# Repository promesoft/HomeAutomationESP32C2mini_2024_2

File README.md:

# HomeAutomationESP32C2mini_2024_2

 Kicad 8

# Purpose
Use for build into berker euro dåser

Two PSU modules and two uP modules

Additional power supply for +-12v and 5v for euro rack synth

## PSU
### 1 - Relay and 230V to 5v
### 2 - LED and 230V to 5v
## uP
### 1 - AM2320 and DS18B20
| ESP Designation  | Pin | Use |
| ------------- | ------------- | ------------- |
| U202 ESP32 C3 | GPIO05 | One Wire 18B20 |
| U202 ESP32 C3 | GPIO06 | SDA AM2320 / HDR |
| U202 ESP32 C3 | GPIO07 | SCL AM2320 / HDR |
| U202 ESP32 C3 | GPIO09 | LED |
| U202 ESP32 C3 | GPIO10 | Relay |
| U202 ESP32 C3 | GPIO21 | Relay Alternative |

### 2 - SSD1306 and AHT10
| ESP Designation  | Pin | Use |
| ------------- | ------------- | ------------- |
| U402 ESP32 C3 | GPIO05 | One Wire 18B20 |
| U402 ESP32 C3 | GPIO06 | SDA SSD1306 / AHT10 |
| U402 ESP32 C3 | GPIO07 | SCL SSD1306 / AHT10 |
| U402 ESP32 C3 | GPIO09 | LED |
| U402 ESP32 C3 | GPIO10 | Relay |
| U402 ESP32 C3 | GPIO21 | Relay Alternative |

## PSU for Euro rack - !!!!! EURORACK HEADER FLIPPED !!!!!!
+/-14v and 7v input

2x 16pin Eurorack power connectors as well as a +/-12v,5v,GND connector

Linear regulators 7805,7812,7912

Fuse blown detection with LED indication

# Status - Preliminary mounted
## Initial 
| Stage  | Detail | Status |
| ------------- | ------------- | ------------- |
| create material  | sch/pcb | OK  |
| | gerber | OK |
| production  |   | OK |
|  | produced | OK |
|  | delivered | OK? |
## Preliminary validation
| Test  | Detail | Status |
| ------------- | ------------- | ------------- |
| Initial Inspection | PWR RLY | OK |
| Initial Inspection | PWR |  |
| Initial Inspection | ESP32C3 OLED| RELAY not working |
|  | | OLED 0,96" not pin-compatible |
| Initial Inspection | ESP32C3 |  |
| Initial Technical Test | PWR RLY+ESP32C3 OLED AHT10 | OK - Blue LED req 820R - 10K pullup removed as impl in ESP32 pullup |
| Initial Technical Test |  |  |
| Initial Technical Test |  |  |
| Initial Product Test | PWR RLY+ESP32C3 OLED AHT10 | OK |
| Initial Product Test |  |  |
| Initial Product Test |  |  |
| Power Draw |  |  |
| Power Draw |  |  |
| Power Draw |  |  |

## Secondary validation
| Test  | Detail | Status |
| ------------- | ------------- |------------- |
| Product Test |  | |
| Product Test |  |  |
| Quality | | |
| Quality | | |
| Long Term Product Test |  |  |
| Power Draw |  |  |
| Power Draw |  |  |
| Power Draw |  |  |

## Errata
### Errata - Sub 1
### Errata - Sub 2
### Errata - Eurorack PSU - !!!!! EURORACK HEADER FLIPPED !!!!!!
| ERROR  | Detail | Workaround |
| ------------- | ------------- |------------- |
| J601 and J602 flipped | -12v on PIN 15+16 - should have been PIN 1+2 | FLIP the header compared to the silkscreen |

## Issues and Notes
### Sub 1
### Sub 2

# Pictures

# Inspiration
https://github.com/pforrmi/KiCad-SSD1306-128x64/tree/master

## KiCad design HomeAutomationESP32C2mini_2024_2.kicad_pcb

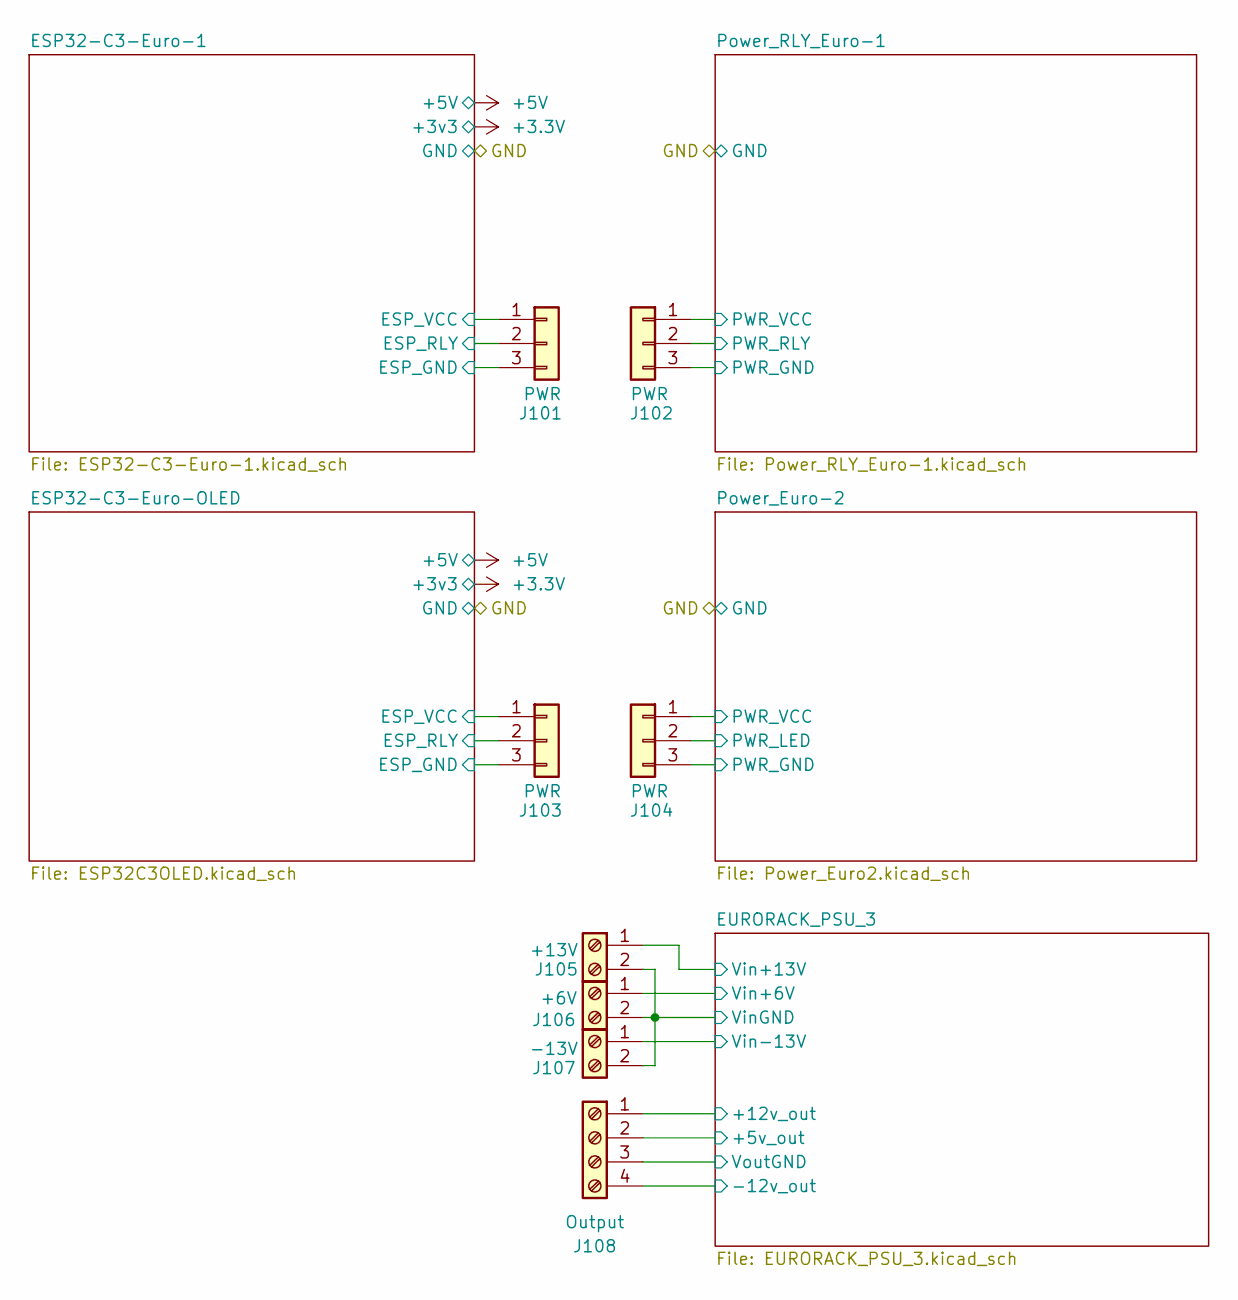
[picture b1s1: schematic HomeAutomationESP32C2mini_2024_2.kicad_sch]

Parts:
J101, J102, J103, J104: PWR; Pins_1x03_2.54mm_TH; Part Number 1-0301FBV0T
J105: +13V; JST_NV_B02P-NV_1x02_P5.00mm_Vertical
J106: +6V; JST_NV_B02P-NV_1x02_P5.00mm_Vertical
J107: -13V; JST_NV_B02P-NV_1x02_P5.00mm_Vertical
J108: Output; TerminalBlock_Phoenix_PT-1,5-4-5.0-H_1x04_P5.00mm_Horizontal

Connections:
/ESP32-C3-Euro-1/ESP_RLY: J101.2; also elsewhere on the board
/ESP32-C3-Euro-1/ESP_VCC: J101.1; also elsewhere on the board
/ESP32-C3-Euro-OLED/ESP_RLY: J103.2; also elsewhere on the board
/ESP32-C3-Euro-OLED/ESP_VCC: J103.1; also elsewhere on the board
/EURORACK_PSU_3/-12v_out: J108.4; also elsewhere on the board
/EURORACK_PSU_3/Vin+6V: J106.1; also elsewhere on the board
/EURORACK_PSU_3/Vin+13V: J105.1; also elsewhere on the board
/EURORACK_PSU_3/Vin-13V: J107.1; also elsewhere on the board
/GND: J101.3, J103.3, J104.3; also elsewhere on the board
/Power_Euro-2/PWR_LED: J104.2; also elsewhere on the board
/Power_Euro-2/PWR_VCC: J104.1; also elsewhere on the board
/Power_RLY_Euro-1/PWR_GND: J102.3; also elsewhere on the board
/Power_RLY_Euro-1/PWR_RLY: J102.2; also elsewhere on the board
/Power_RLY_Euro-1/PWR_VCC: J102.1; also elsewhere on the board

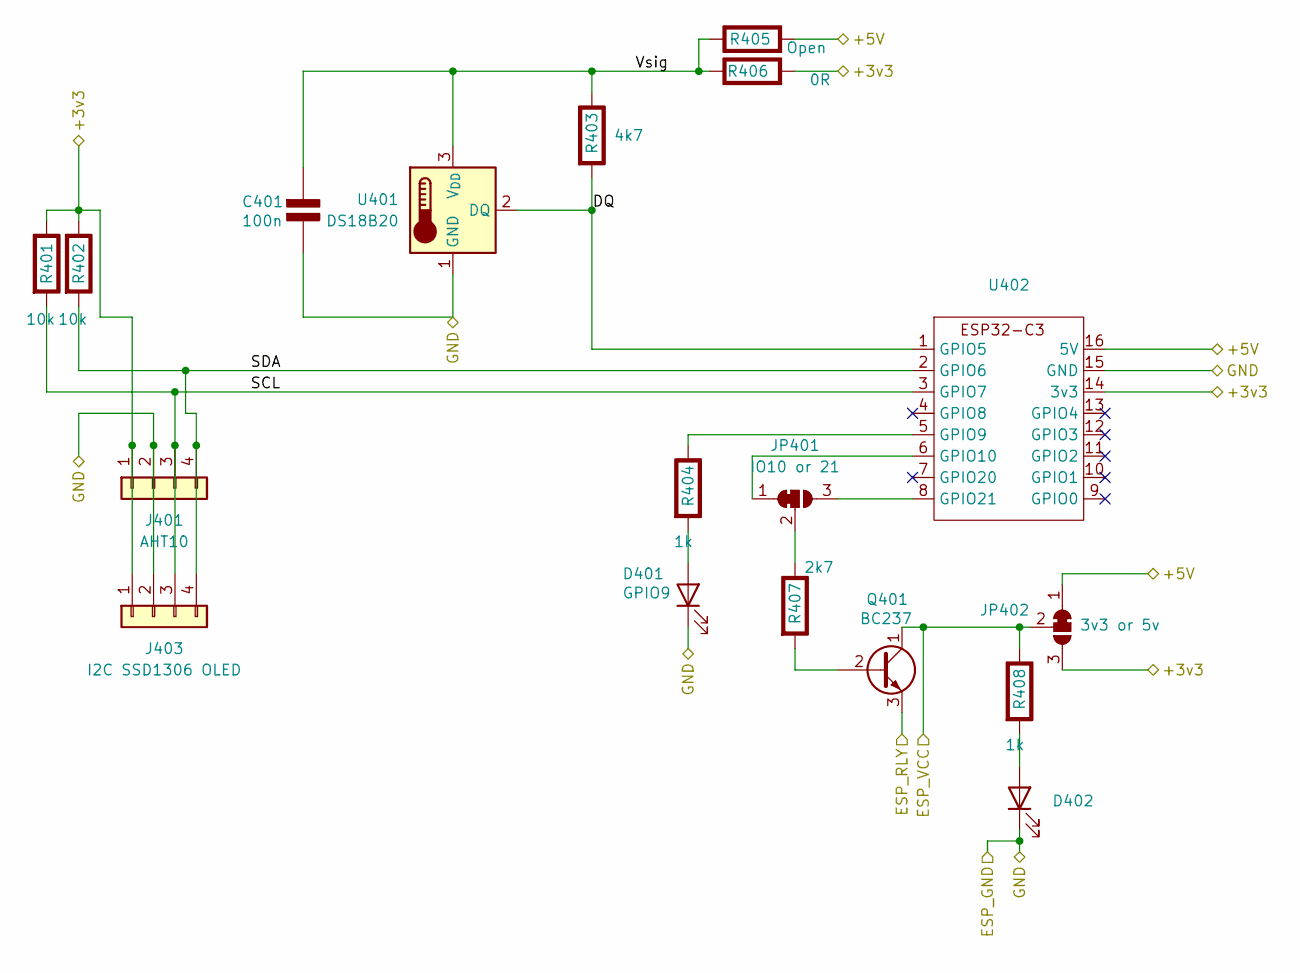
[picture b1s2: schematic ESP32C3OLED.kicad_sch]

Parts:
C401: 100n; C_0805_2012Metric; Rating V
D401: GPIO9; LED_D3.0mm
D402: PWR; LED_D3.0mm
J401: AHT10; Pins_1x04_2.54mm_TH
J403: I2C SSD1306 OLED; 128x64OLED
JP401: IO10 or 21; SolderJumper-3_P1.3mm_Bridged12_RoundedPad1.0x1.5mm_NumberL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
JP402: 3v3 or 5v; SolderJumper-3_P1.3mm_Bridged12_RoundedPad1.0x1.5mm_NumberL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
Q401: BC237; TO-92_Inline
R401, R402: 10k; R_0805_2012Metric; Rating W
R403: 4k7; R_0805_2012Metric; Rating W
R404, R408: 1k; R_0805_2012Metric; Rating W
R405: Open; R_0805_2012Metric; Rating W
R406: 0R; R_0805_2012Metric; Rating W
R407: 2k7; R_0805_2012Metric; Rating W
U401: DS18B20; TO-92_Inline
U402: ESP32-C3-Supermini

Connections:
+3.3V: J401.1, J403.1, JP402.3 (B), R401.1 (+), R402.1 (+), R406.2 (-), U402.14 (3v3); also elsewhere on the board
+5V: JP402.1 (A), R405.2 (-), U402.16 (5V); also elsewhere on the board
/ESP32-C3-Euro-OLED/DQ: R403.2 (-), U401.2 (DQ), U402.1 (GPIO5)
/ESP32-C3-Euro-OLED/ESP_RLY: Q401.3 (E); also elsewhere on the board
/ESP32-C3-Euro-OLED/ESP_VCC: JP402.2 (C), Q401.1 (C), R408.1 (+); also elsewhere on the board
/ESP32-C3-Euro-OLED/SCL: J401.3, J403.3, R401.2 (-), U402.3 (GPIO7)
/ESP32-C3-Euro-OLED/SDA: J401.4, J403.4, R402.2 (-), U402.2 (GPIO6)
/ESP32-C3-Euro-OLED/Vsig: C401.1 (+), R403.1 (+), R405.1 (+), R406.1 (+), U401.3 (V_{DD})
/GND: C401.2 (-), D401.1 (K), D402.1 (K), J401.2, J403.2, U401.1 (GND), U402.15 (GND); also elsewhere on the board
unnamed: D401.2 (A), R404.2 (-)
unnamed: D402.2 (A), R408.2 (-)
unnamed: JP401.1 (A), U402.6 (GPIO10)
unnamed: JP401.3 (B), U402.8 (GPIO21)
unnamed: JP401.2 (C), R407.1 (+)
unnamed: Q401.2 (B), R407.2 (-)
unnamed: R404.1 (+), U402.5 (GPIO9)

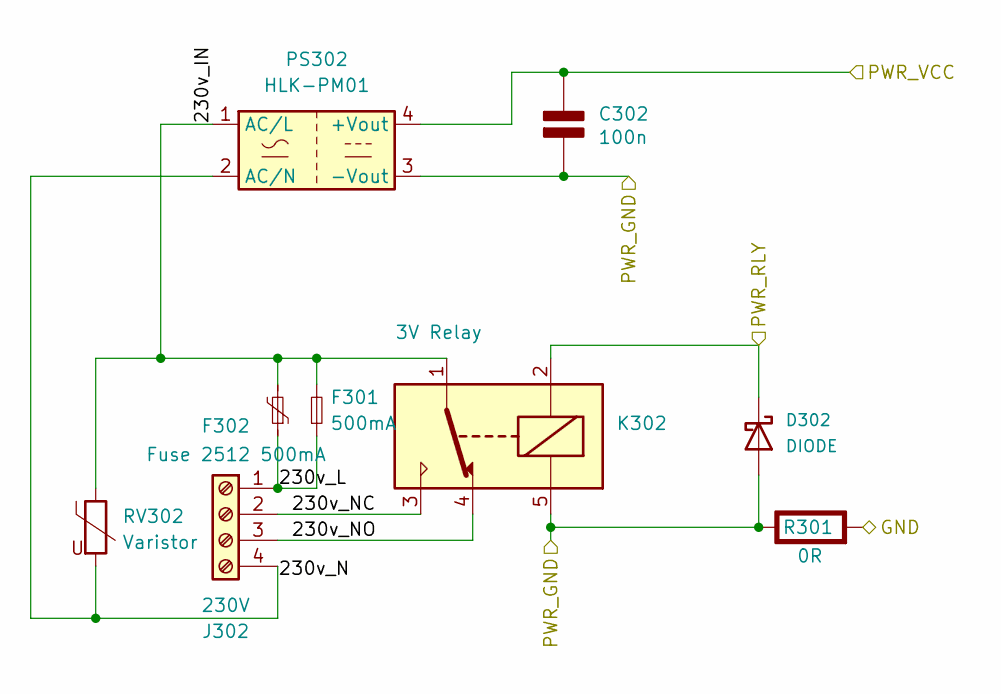
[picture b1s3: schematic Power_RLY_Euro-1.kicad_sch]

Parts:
C302: 100n; C_0805_2012Metric; Rating V
D302: DIODE; D_DO-41_SOD81_P10.16mm_Horizontal
F301: 500mA; Fuse_Littelfuse-NANO2-462
F302: Fuse 2512 500mA; Fuse_2512_6332Metric_Pad1.52x3.35mm_HandSolder
J302: 230V; TerminalBlock_Phoenix_PT-1,5-4-5.0-H_1x04_P5.00mm_Horizontal
K302: 3V Relay; Relay_SPDT_SANYOU_SRD_Series_Form_C
PS302: HLK-PM01; Converter_ACDC_Hi-Link_HLK-PMxx
R301: 0R; R_0805_2012Metric; Rating W
RV302: Varistor; RV_Disc_D9mm_W4.8mm_P5mm

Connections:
/GND: R301.2 (-); also elsewhere on the board
/Power_RLY_Euro-1/230v_IN: F301.2, F302.2, K302.1, PS302.1 (AC/L), RV302.1
/Power_RLY_Euro-1/230v_L: F301.1, F302.1, J302.1
/Power_RLY_Euro-1/230v_N: J302.4, PS302.2 (AC/N), RV302.2
/Power_RLY_Euro-1/230v_NC: J302.2, K302.3
/Power_RLY_Euro-1/230v_NO: J302.3, K302.4
/Power_RLY_Euro-1/PWR_GND: C302.2 (-), D302.2 (A), K302.5, PS302.3 (-Vout), R301.1 (+); also elsewhere on the board
/Power_RLY_Euro-1/PWR_RLY: D302.1 (K), K302.2; also elsewhere on the board
/Power_RLY_Euro-1/PWR_VCC: C302.1 (+), PS302.4 (+Vout); also elsewhere on the board

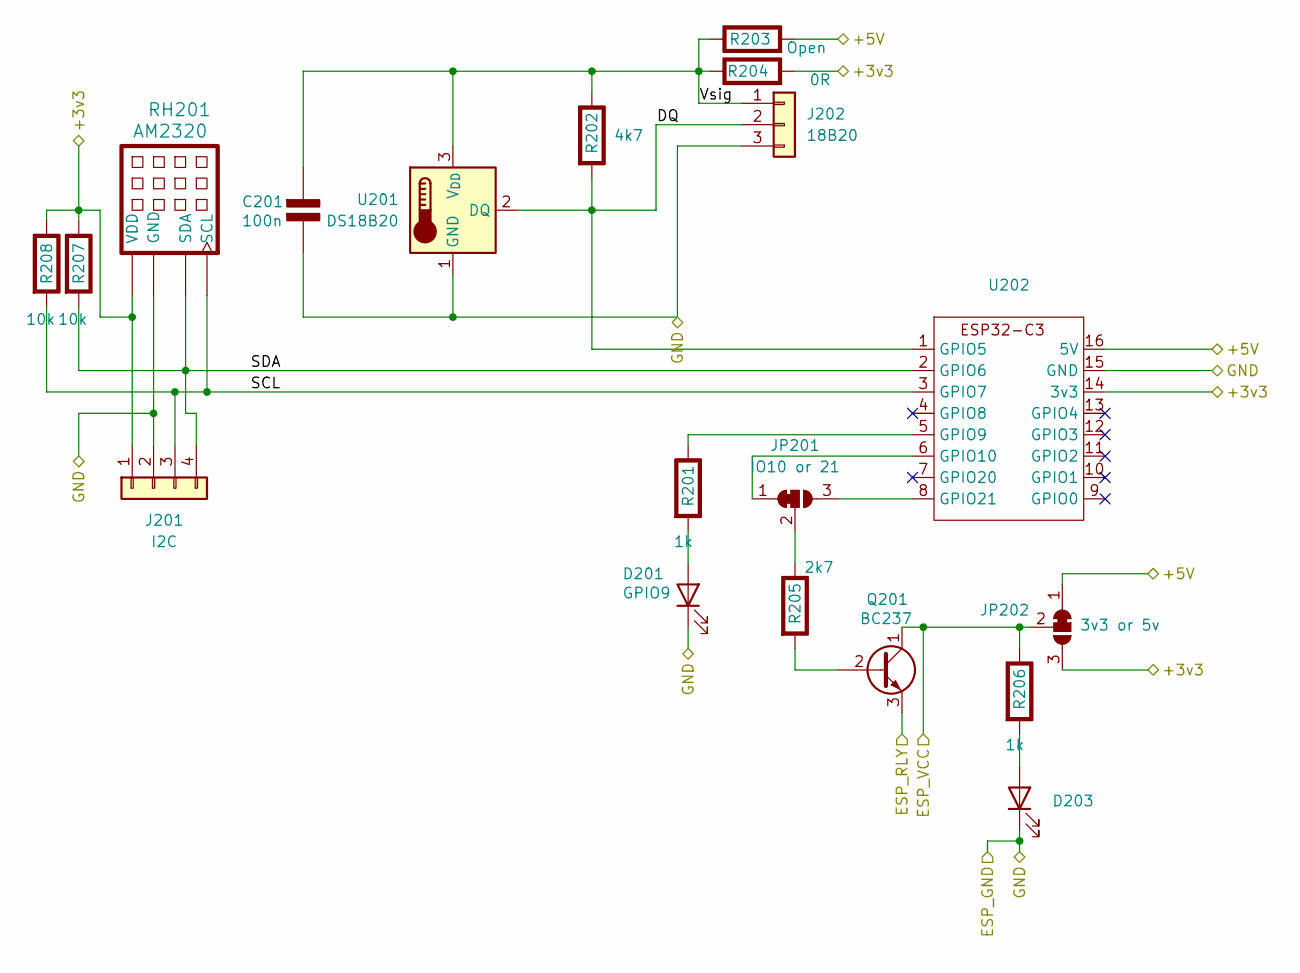
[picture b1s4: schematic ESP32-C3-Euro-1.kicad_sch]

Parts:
C201: 100n; C_0805_2012Metric; Rating V
D201: GPIO9; LED_D3.0mm
D203: PWR; LED_D3.0mm
J201: I2C; Pins_1x04_2.54mm_TH
J202: 18B20; Pins_1x03_2.54mm_TH; Part Number 1-0301FBV0T
JP201: IO10 or 21; SolderJumper-3_P1.3mm_Bridged12_RoundedPad1.0x1.5mm_NumberL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
JP202: 3v3 or 5v; SolderJumper-3_P1.3mm_Bridged12_RoundedPad1.0x1.5mm_NumberL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
Q201: BC237; TO-92_Inline
R201, R206: 1k; R_0805_2012Metric; Rating W
R202: 4k7; R_0805_2012Metric; Rating W
R203: Open; R_0805_2012Metric; Rating W
R204: 0R; R_0805_2012Metric; Rating W
R205: 2k7; R_0805_2012Metric; Rating W
R207, R208: 10k; R_0805_2012Metric; Rating W
RH201: AM2320; ASAIR_AM2302_P2.54mm_Vertical
U201: DS18B20; TO-92_Inline
U202: ESP32-C3-Supermini

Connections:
+3.3V: J201.1, JP202.3 (B), R204.2 (-), R207.1 (+), R208.1 (+), RH201.1 (VDD), U202.14 (3v3); also elsewhere on the board
+5V: JP202.1 (A), R203.2 (-), U202.16 (5V); also elsewhere on the board
/ESP32-C3-Euro-1/DQ: J202.2, R202.2 (-), U201.2 (DQ), U202.1 (GPIO5)
/ESP32-C3-Euro-1/ESP_RLY: Q201.3 (E); also elsewhere on the board
/ESP32-C3-Euro-1/ESP_VCC: JP202.2 (C), Q201.1 (C), R206.1 (+); also elsewhere on the board
/ESP32-C3-Euro-1/SCL: J201.3, R208.2 (-), RH201.4 (SCL), U202.3 (GPIO7)
/ESP32-C3-Euro-1/SDA: J201.4, R207.2 (-), RH201.2 (SDA), U202.2 (GPIO6)
/ESP32-C3-Euro-1/Vsig: C201.1 (+), J202.1, R202.1 (+), R203.1 (+), R204.1 (+), U201.3 (V_{DD})
/GND: C201.2 (-), D201.1 (K), D203.1 (K), J201.2, J202.3, RH201.3 (GND), U201.1 (GND), U202.15 (GND); also elsewhere on the board
unnamed: D201.2 (A), R201.2 (-)
unnamed: D203.2 (A), R206.2 (-)
unnamed: JP201.1 (A), U202.6 (GPIO10)
unnamed: JP201.3 (B), U202.8 (GPIO21)
unnamed: JP201.2 (C), R205.1 (+)
unnamed: Q201.2 (B), R205.2 (-)
unnamed: R201.1 (+), U202.5 (GPIO9)

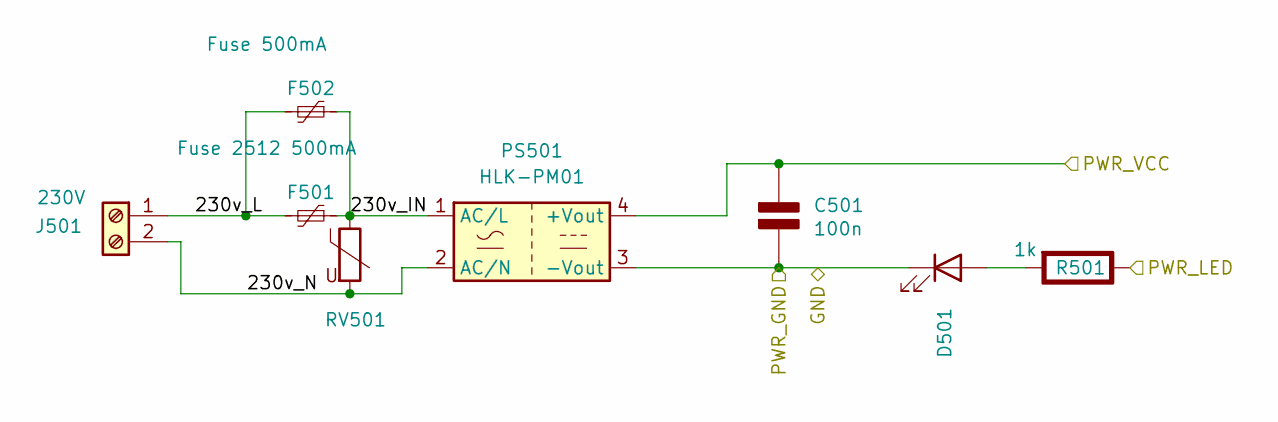
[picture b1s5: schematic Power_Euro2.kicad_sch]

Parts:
C501: 100n; C_0805_2012Metric; Rating V
D501: PWR; LED_0805_2012Metric_Pad1.15x1.40mm_HandSolder
F501: Fuse 2512 500mA; Fuse_2512_6332Metric_Pad1.52x3.35mm_HandSolder
F502: Fuse 500mA; L_Axial_L7.0mm_D3.3mm_P5.08mm_Vertical_Fastron_MICC
J501: 230V; JST_NV_B02P-NV_1x02_P5.00mm_Vertical
PS501: HLK-PM01; Converter_ACDC_Hi-Link_HLK-PMxx
R501: 1k; R_0805_2012Metric; Rating W
RV501: Varistor; RV_Disc_D9mm_W4.8mm_P5mm

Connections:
/GND: C501.2 (-), D501.1 (K), PS501.3 (-Vout); also elsewhere on the board
/Power_Euro-2/230v_IN: F501.1, F502.1, PS501.1 (AC/L), RV501.1
/Power_Euro-2/230v_L: F501.2, F502.2, J501.1
/Power_Euro-2/230v_N: J501.2, PS501.2 (AC/N), RV501.2
/Power_Euro-2/PWR_LED: R501.1 (+); also elsewhere on the board
/Power_Euro-2/PWR_VCC: C501.1 (+), PS501.4 (+Vout); also elsewhere on the board
unnamed: D501.2 (A), R501.2 (-)

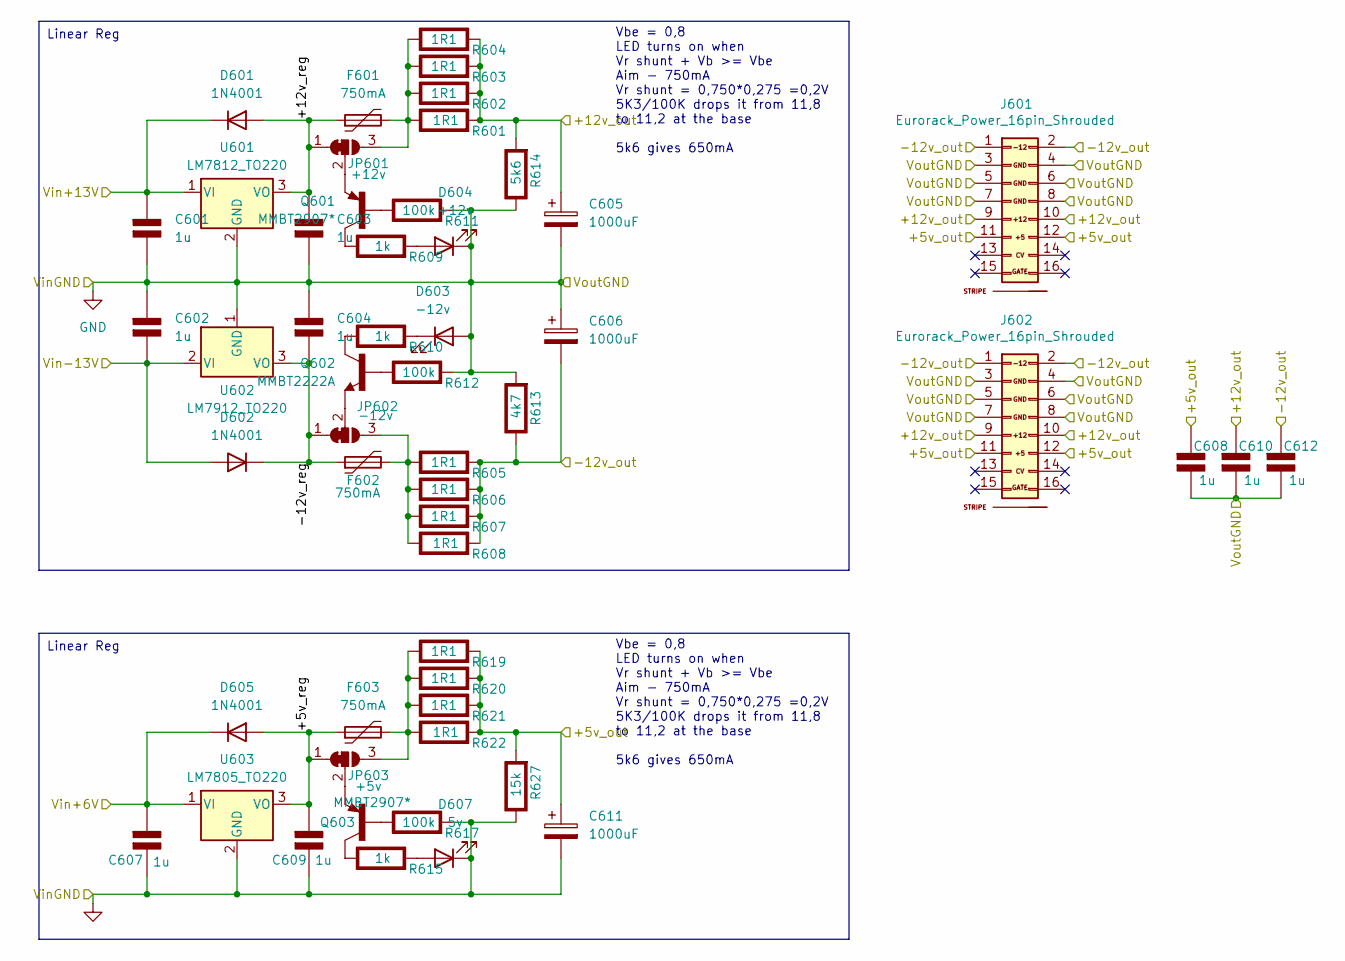
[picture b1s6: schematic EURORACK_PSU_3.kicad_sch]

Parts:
C601, C602, C603, C604, C607, C608, C609, C610, C612: 1u; C_0805_AJ; Rating V
C605, C606, C611: 1000uF; CP_Radial_D10.0mm_P5.00mm
D601, D602, D605: 1N4001; D_DO-41_SOD81_P10.16mm_Horizontal
D603: -12v; D_0805_AJ
D604: +12v; D_0805_AJ
D607: 5v; D_0805_AJ
F601, F602, F603: 750mA; Fuse_1812_4532Metric
J601, J602: Eurorack_Power_16pin_Shrouded; IDC-Header_2x08_P2.54mm_Vertical; Part Number LL1007-1 (2*8 HITEMP)
JP601: +12v; SolderJumper-3_P1.3mm_Bridged12_RoundedPad1.0x1.5mm_NumberL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
JP602: -12v; SolderJumper-3_P1.3mm_Bridged12_RoundedPad1.0x1.5mm_NumberL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
JP603: +5v; SolderJumper-3_P1.3mm_Bridged12_RoundedPad1.0x1.5mm_NumberL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
Q601, Q603: MMBT2907*; SOT-23
Q602: MMBT2222A; SOT-23
R601, R602, R603, R604, R605, R606, R607, R608, R619, R620, R621, R622: 1R1; R_0805_AJ; Rating W
R609, R610, R615: 1k; R_0805_AJ; Rating W
R611, R612, R617: 100k; R_0805_AJ; Rating W
R613: 4k7; R_0805_AJ; Rating W
R614: 5k6; R_0805_AJ; Rating W
R627: 15k; R_0805_AJ; Rating W
U601: LM7812_TO220; TO-220-3_Vertical
U602: LM7912_TO220; TO-220-3_Vertical
U603: LM7805_TO220; TO-220-3_Vertical

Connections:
/EURORACK_PSU_3/+5v_reg: C609.1 (+), D605.2 (A), F603.1, JP603.1 (A), U603.3 (VO)
/EURORACK_PSU_3/+12v_reg: C603.1 (+), D601.2 (A), F601.1, JP601.1 (A), U601.3 (VO)
/EURORACK_PSU_3/-12v_out: C606.2, C612.1 (+), J601.1, J601.2, J601.15 (-12V), J601.16, J602.1, J602.2, J602.15 (-12V), J602.16, R605.2 (-), R606.2 (-), R607.2 (-), R608.2 (-), R613.1 (+); also elsewhere on the board
/EURORACK_PSU_3/-12v_reg: C604.2 (-), D602.1 (K), F602.1, JP602.1 (A), U602.3 (VO)
/EURORACK_PSU_3/Vin+6V: C607.1 (+), D605.1 (K), U603.1 (VI); also elsewhere on the board
/EURORACK_PSU_3/Vin+13V: C601.1 (+), D601.1 (K), U601.1 (VI); also elsewhere on the board
/EURORACK_PSU_3/Vin-13V: C602.2 (-), D602.2 (A), U602.2 (VI); also elsewhere on the board
unnamed: D603.1 (K), R610.2 (-)
unnamed: D604.2 (A), R609.2 (-)
unnamed: D607.2 (A), R615.2 (-)
unnamed: F601.2, JP601.3 (B), R601.1 (+), R602.1 (+), R603.1 (+), R604.1 (+)
unnamed: JP601.2 (C), Q601.2 (E)
unnamed: F602.2, JP602.3 (B), R605.1 (+), R606.1 (+), R607.1 (+), R608.1 (+)
unnamed: JP602.2 (C), Q602.2 (E)
unnamed: F603.2, JP603.3 (B), R619.1 (+), R620.1 (+), R621.1 (+), R622.1 (+)
unnamed: JP603.2 (C), Q603.2 (E)
unnamed: Q601.1 (B), R611.1 (+)
unnamed: Q601.3 (C), R609.1 (+)
unnamed: Q602.1 (B), R612.1 (+)
unnamed: Q602.3 (C), R610.1 (+)
unnamed: Q603.1 (B), R617.1 (+)
unnamed: Q603.3 (C), R615.1 (+)

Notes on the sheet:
Linear Reg
Vbe = 0,8 LED turns on when Vr shunt + Vb >= Vbe Aim - 750mA Vr shunt = 0,750*0,275 =0,2V 5K3/100K drops it from 11,8 to 11,2 at the base 5k6 gives 650mA

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
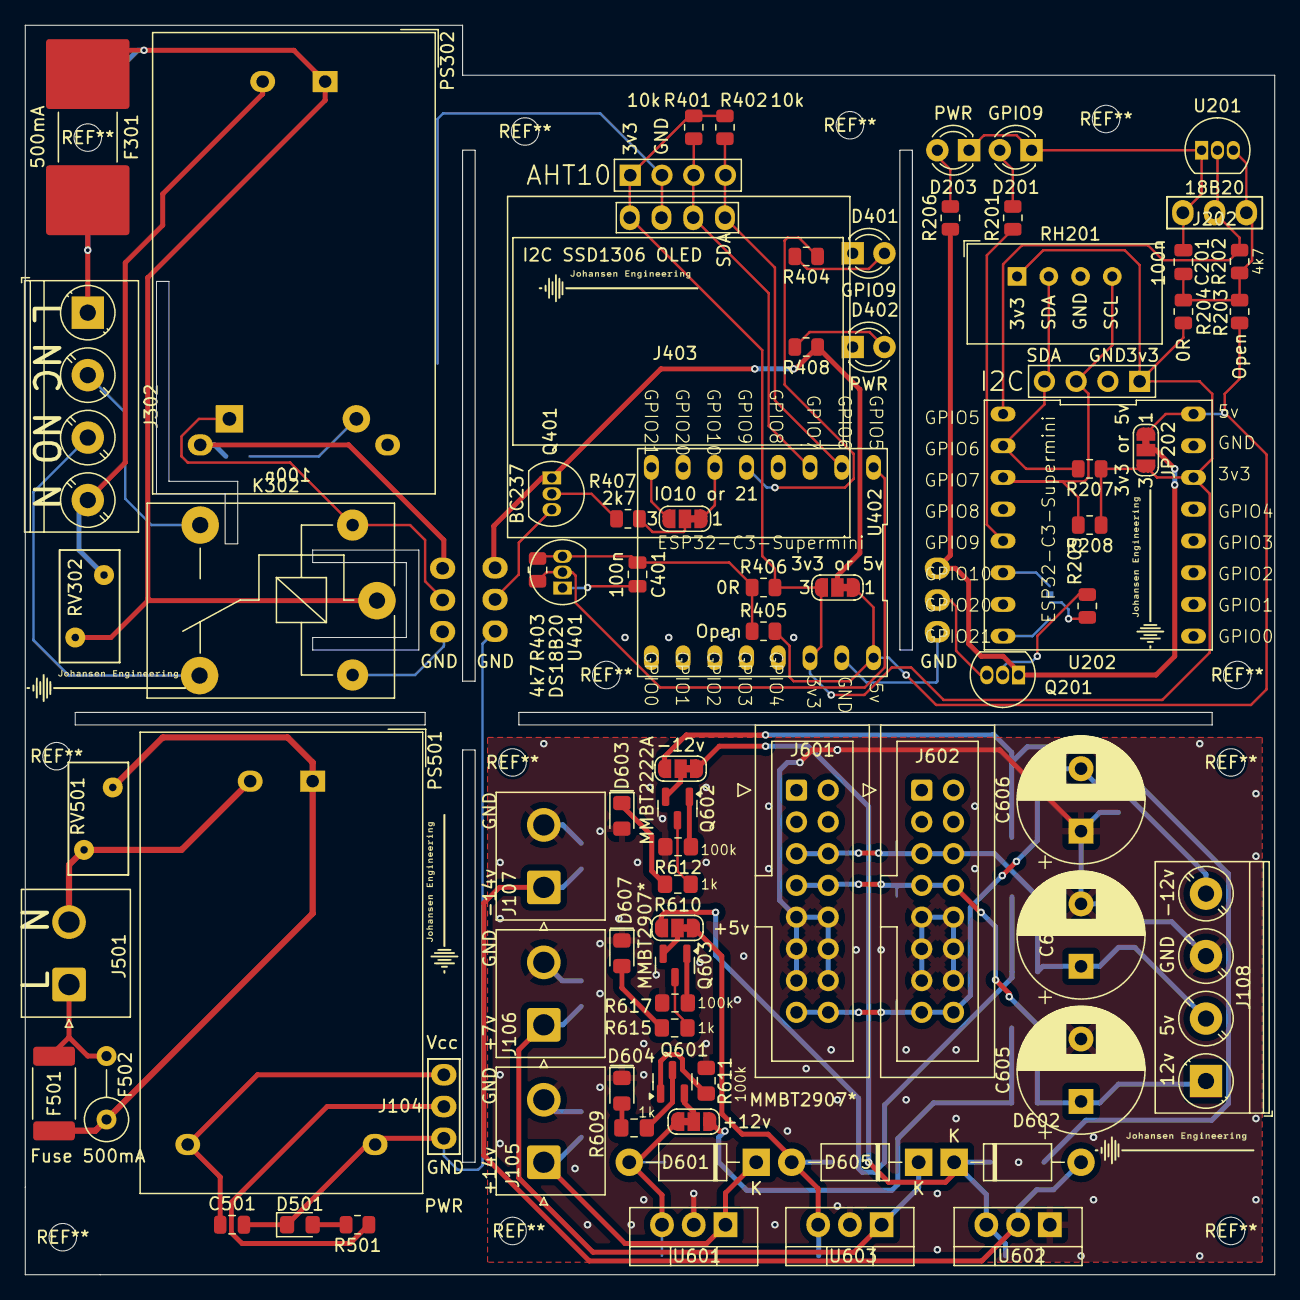
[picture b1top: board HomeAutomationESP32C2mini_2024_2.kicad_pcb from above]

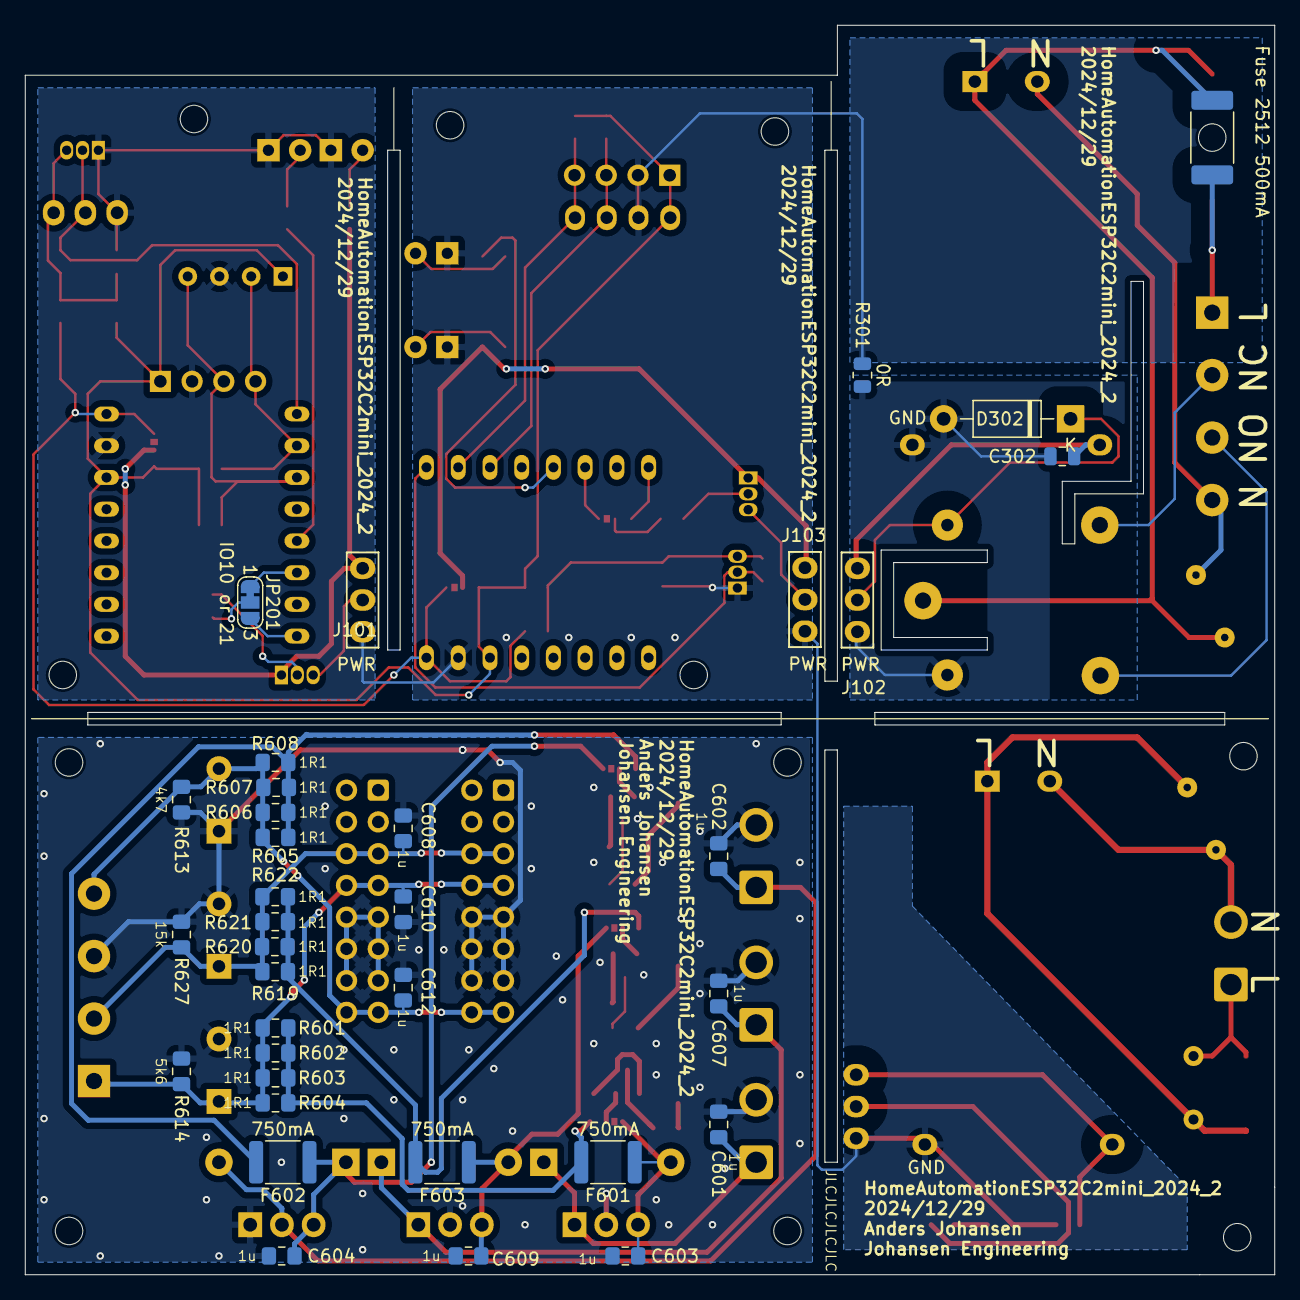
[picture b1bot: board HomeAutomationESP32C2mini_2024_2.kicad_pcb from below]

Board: 2 copper layers, 100.0 x 100.0 mm, 115 parts (35 on the bottom side), 68 nets.

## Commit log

2024-12-30 Update README.md
    initial template
2024-12-30 Update README.md
    HomeAutomationESP32C2mini_2024_2.jpg
2025-01-02 Update README.md
    in progress
2025-01-17 Misc
2025-01-17 Project Pictures
2025-01-24 VCO3 test
2025-01-26 Picture Update
